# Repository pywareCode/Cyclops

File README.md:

ANDY
=======

Meet Andy, a multi-purpose humanoid robot built with a Raspberry Pi and a robosapien toy. Andy can walk, pick up and set down objects, take pictures, record video, and answer questions. Andy is voice controlled, so there is no need for a computer or smart phone to send him commands. Just say "Andy" wait for the beep, say your command, and Andy will do the rest.

Hardware
========

Andy is built out of inexpencive hardware, so no need for pocket loads of cash. A Robosapien is used for the body, making it easy to use and light in maintainance. A Raspberry Pi is the brain of Andy, making him a very intelligent machine. A cheap USB microphone is plugged into the Raspberry Pi's USB socket giving Andy ears. L298N and L293D motor drivers are used to control Andy's motors, and a MCP23017 chip is used to give the Raspberry Pi more General Purpose Input and Output ports (GPIO). Andy has vision with a Raspberry Pi CSI camera. With all of this powerful hardware, it makes a toy robot a very useful helper.

Software
========

Andy uses many different software packages to operate. Pocketsphinx is used for speech recognition, OpenCV is used for the vision, MySQL is used for Andy's database, and Python is used to combine everything together.

Learn More
==========

To learn more about the Andy Project and how you can make your own Andy, go to Andy's page on <a href="http://hackaday.io/project/1205">Hackaday.io</a>.
Also, check out <a href="http://youtu.be/Y5uNffNiwK4">a video</a> of Andy in action.

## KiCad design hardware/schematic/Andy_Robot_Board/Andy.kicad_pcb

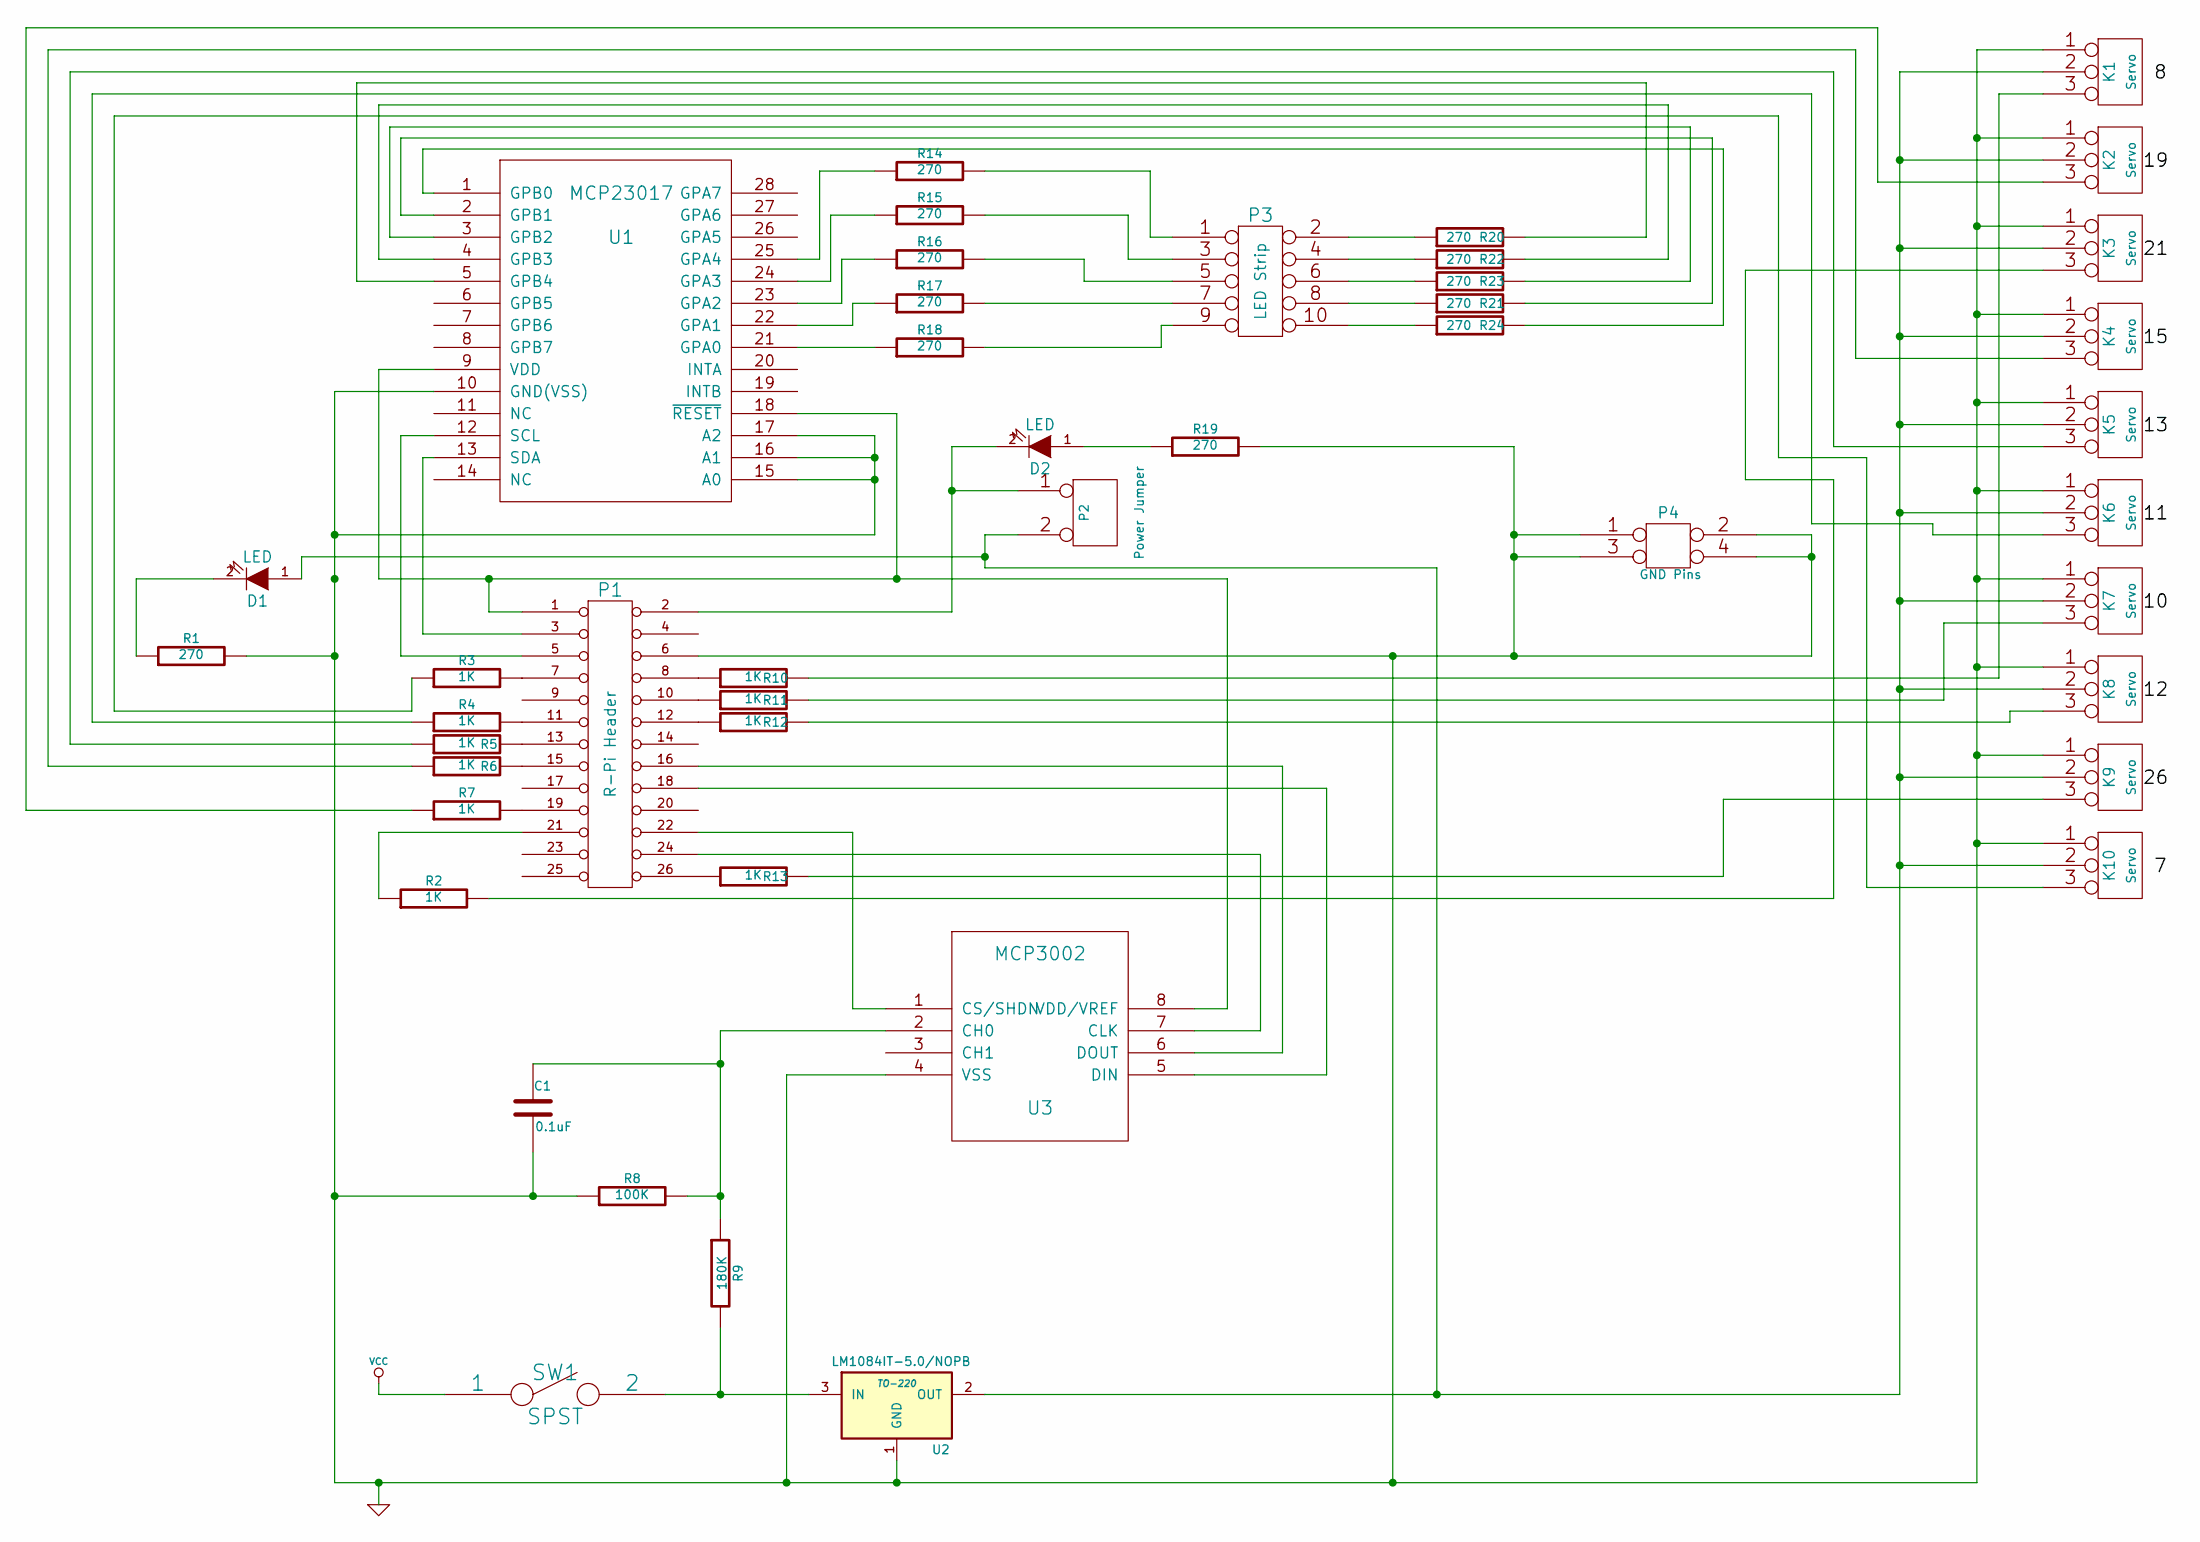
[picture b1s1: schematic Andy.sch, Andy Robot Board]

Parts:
C1: 0.1uF
D1, D2: LED
K1, K2, K3, K4, K5, K6, K7, K8, K9, K10: Servo
P1: R-Pi Header
P2: Power Jumper
P3: LED Strip
P4: GND Pins
R1, R14, R15, R16, R17, R18, R19, R20, R21, R22, R23, R24: 270
R2, R3, R4, R5, R6, R7, R10, R11, R12, R13: 1K
R8: 100K
R9: 180K
SW1: SPST
U1: MCP23017
U2: LM1084IT-5.0/NOPB; TO-220
U3: MCP3002

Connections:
GND: C1.2, K1.1, K2.1, K3.1, K4.1, K5.1, K6.1, K7.1, K8.1, K9.1, K10.1, P1.6, P4.1, P4.2, P4.3, P4.4, R1.2, R8.1, R19.2, U1.10 (GND(VSS)), U1.15 (A0), U1.16 (A1), U1.17 (A2), U2.1 (GND), U3.4 (VSS)
unnamed: R22.2, U1.3 (GPB2)
unnamed: R24.2, U1.1 (GPB0)
unnamed: P3.10, R24.1
unnamed: P3.8, R23.1
unnamed: P3.6, R22.1
unnamed: P3.4, R21.1
unnamed: P3.2, R20.1
unnamed: R20.2, U1.5 (GPB4)
unnamed: R21.2, U1.4 (GPB3)
unnamed: R23.2, U1.2 (GPB1)
unnamed: K10.3, R3.1
unnamed: K5.3, R5.1
unnamed: D2.1 (A), R19.1
unnamed: K4.3, R6.1
unnamed: P3.1, R14.2
unnamed: R14.1, U1.25 (GPA4)
unnamed: R15.1, U1.24 (GPA3)
unnamed: R16.1, U1.23 (GPA2)
unnamed: R17.1, U1.22 (GPA1)
unnamed: P3.3, R15.2
unnamed: P3.5, R16.2
unnamed: P3.7, R17.2
unnamed: P3.9, R18.2
unnamed: K2.3, R7.1
unnamed: D2.2 (K), P1.2, P2.1
unnamed: P1.7, R3.2
unnamed: P1.19, R7.2
unnamed: P1.15, R6.2
unnamed: P1.13, R5.2
unnamed: P1.11, R4.2
unnamed: D1.2 (K), R1.1
unnamed: K6.3, R4.1
unnamed: P1.26 (P22), R13.1
unnamed: K9.3, R13.2
unnamed: P1.12, R12.1
unnamed: P1.10, R11.1
unnamed: K1.3, R10.2
unnamed: P1.8, R10.1
unnamed: P1.21, R2.1
unnamed: K3.3, R2.2
unnamed: R18.1, U1.21 (GPA0)
unnamed: K7.3, R11.2
unnamed: K8.3, R12.2
unnamed: P1.24 (P20), U3.7 (CLK)
unnamed: C1.1, R8.2, R9.1, U3.2 (CH0)
unnamed: P1.22, U3.1 (CS/SHDN)
unnamed: P1.18, U3.5 (DIN)
unnamed: P1.16, U3.6 (DOUT)
unnamed: P1.3, U1.13 (SDA)
unnamed: P1.5, U1.12 (SCL)
unnamed: D1.1 (A), K1.2 (PM), K2.2 (PM), K3.2 (PM), K4.2 (PM), K5.2 (PM), K6.2 (PM), K7.2 (PM), K8.2 (PM), K9.2 (PM), K10.2 (PM), P2.2 (PM), U2.2 (OUT)
unnamed: P1.1, U1.9 (VDD), U1.18 (~RESET), U3.8 (VDD/VREF)
unnamed: R9.2, SW1.2, U2.3 (IN)

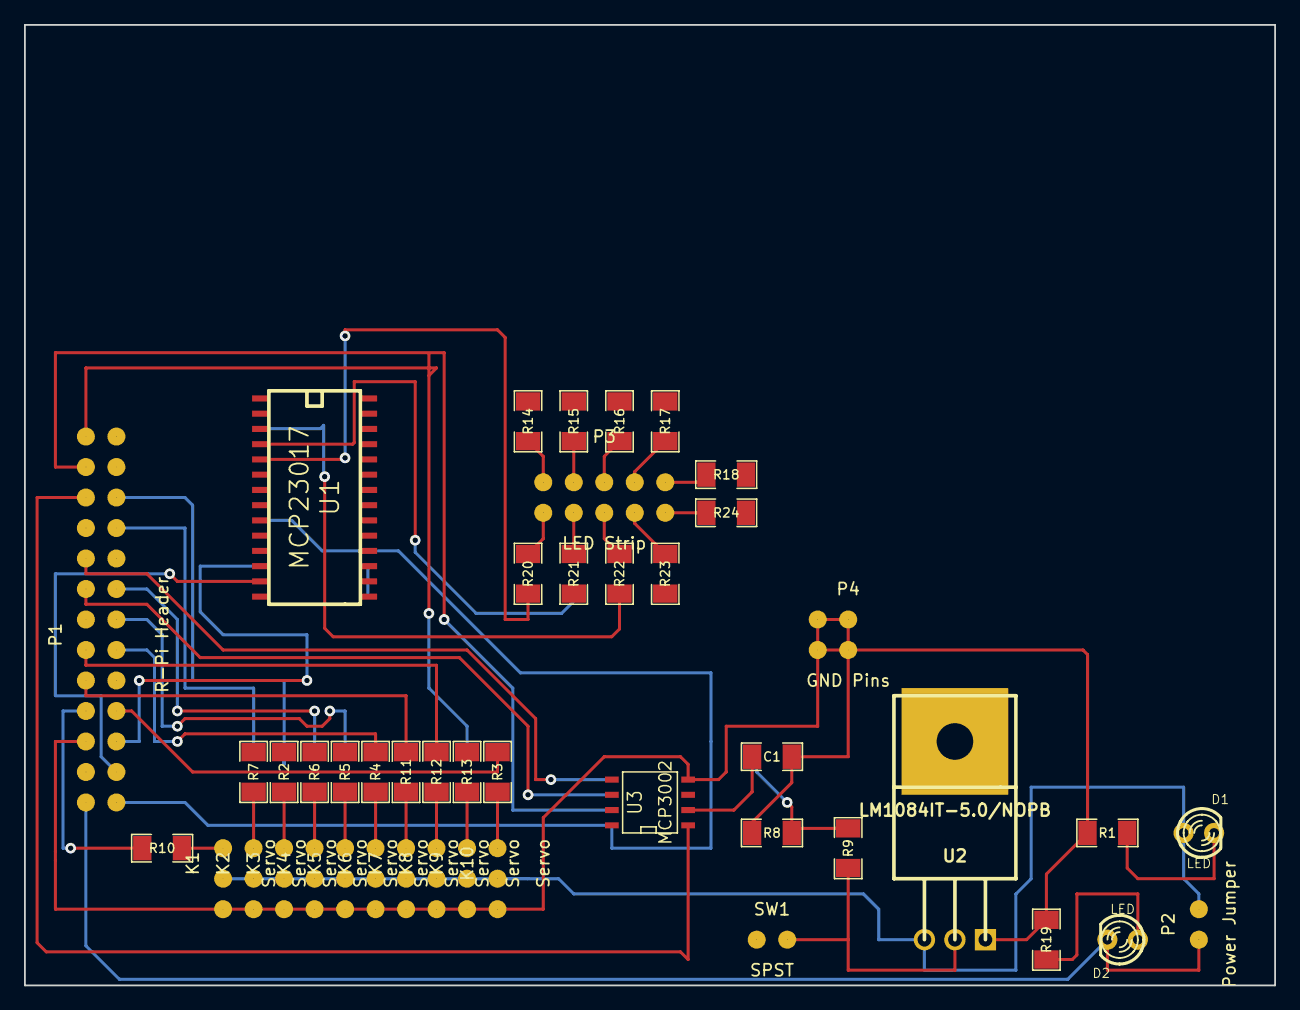
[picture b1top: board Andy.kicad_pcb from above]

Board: 2 copper layers, 104.1 x 80.0 mm, 45 parts (0 on the bottom side), 54 nets.

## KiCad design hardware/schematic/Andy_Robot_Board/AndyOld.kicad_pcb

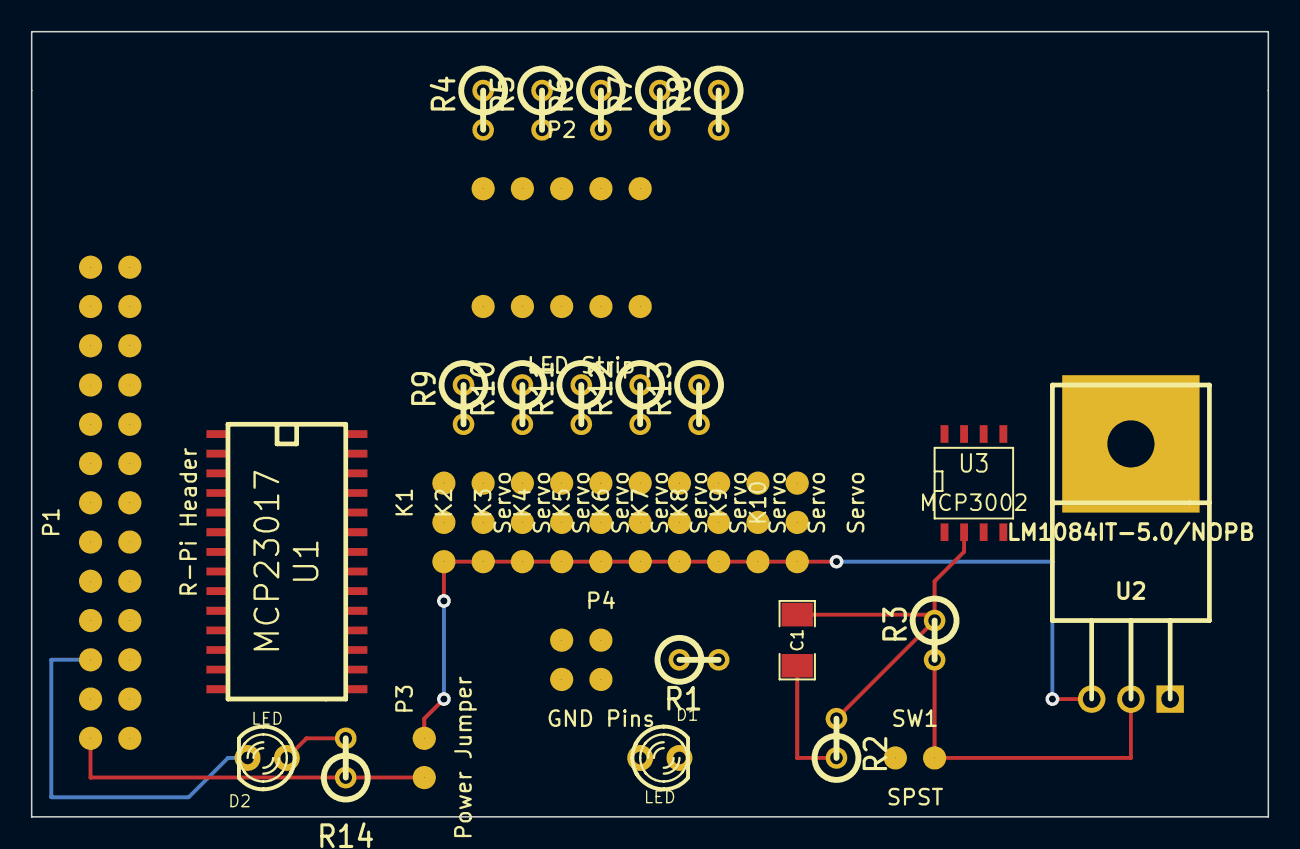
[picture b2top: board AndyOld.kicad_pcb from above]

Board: 2 copper layers, 80.0 x 50.8 mm, 35 parts (0 on the bottom side), 44 nets.

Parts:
C1: 0.1uF; SM1206
D1, D2: LED; LED-3MM
K1, K2, K3, K4, K5, K6, K7, K8, K9, K10: Servo; ServoHeader
P1: R-Pi Header; RaspberryPiHeader
P2: LED Strip; LED-Bar-Graph
P3: Power Jumper; jumper
P4: GND Pins; GNDheader
R1, R4, R5, R6, R7, R8, R9, R10, R11, R12, R13, R14: R; R1
R2: 100K; R1
R3: 180K; R1
SW1: SPST; jumper
U1: MCP23017; SO28
U2: LM1084IT-5.0/NOPB; TO220
U3: MCP3002; SO8N

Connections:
GND: C1.2, D1.2, D2.2, K6.3, K7.3, K8.3, K9.3, K10.3, P1.6, P4.1, P4.2, P4.3, P4.4, R2.1, U1.10, U1.15, U1.16, U1.17, U2.1, U3.4
unnamed: K9.2, P1.26
unnamed: K8.2, P1.12
unnamed: K7.2, P1.10
unnamed: K1.2, P1.21
unnamed: R4.1, U1.25
unnamed: R5.1, U1.24
unnamed: K1.3, K2.3, K3.3, K4.3, K5.3, K6.2, P1.8
unnamed: K10.2, P1.7
unnamed: K3.2, P1.15
unnamed: K4.2, P1.13
unnamed: K5.2, P1.11
unnamed: R6.1, U1.23
unnamed: R7.1, U1.22
unnamed: P2.1, R4.2
unnamed: P2.3, R5.2
unnamed: P2.5, R6.2
unnamed: P2.7, R7.2
unnamed: P2.9, R8.2
unnamed: R8.1, U1.21
unnamed: R11.2, U1.3
unnamed: R12.2, U1.2
unnamed: R13.2, U1.1
unnamed: P2.10, R13.1
unnamed: P2.8, R12.1
unnamed: P2.6, R11.1
unnamed: P2.4, R10.1
unnamed: P2.2, R9.1
unnamed: R9.2, U1.5
unnamed: R10.2, U1.4
unnamed: D2.1, R14.2
unnamed: P1.2, P3.1, R14.1
unnamed: D1.1, R1.1
unnamed: K2.2, P1.19
unnamed: R3.2, SW1.2, U2.3
unnamed: P1.18, U3.5
unnamed: P1.16, U3.6
unnamed: P1.3, U1.13
unnamed: P1.5, U1.12
unnamed: P1.1, U1.9, U1.18, U3.8
unnamed: P1.22, U3.1
unnamed: K1.1, K2.1, K3.1, K4.1, K5.1, K6.1, K7.1, K8.1, K9.1, K10.1, P3.2, R1.2, U2.2
unnamed: P1.24, U3.7
unnamed: C1.1, R2.2, R3.1, U3.2

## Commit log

2014-02-22 Added Google Speech-To-Text
2014-02-24 Added main.py and created functions
2014-02-24 added more cmds
2014-02-25 Added math
2014-02-26 Updated .gitgnore
2014-02-26 Deleted unwanted files
2014-03-01 Changed some files
2014-03-01 Added time knowledge
2014-03-01 Added me() function
2014-03-02 Added Walk() class and functions
2014-03-11 Added Motor Schematic and Arm() class
2014-03-11 Added Where() class
2014-03-11 Added Take() class
2014-03-11 Added Tell() class
2014-03-18 Added GPIO pin test and MCP23017 tst.
2014-03-19 added .autosave
2014-03-21 Added text-to-speech
2014-03-28 Updated text to speech
2014-04-07 Added motor control using L298N driver board. Also added PWM support
2014-04-08 Added Client Program
2014-04-08 Added server
2014-04-08 Removed .flac from .gitgnore for test
2014-04-09 Working Windows Version
    This is a working version for Windows. Use if revert is needed.
2014-04-18 Working Raspberry Pi version. MCP23017 now working with L293D in MCP.py
2014-04-30 Updated Schematic to 1.4
    Fixed control line errors, motor driver errors, and enable error.
2014-05-08 Worked on motor driving.
2014-05-13 Edited motor.py
2014-05-13 Updated language model
2014-05-20 Rearranged file system
2014-05-20 Added database file
2014-05-21 Added people and object access to database
2014-05-21 Updated schematic and language model
2014-05-22 Added complete 'WHO' command
2014-05-22 Added 'shutdown' command.
2014-05-23 Modified permissions and added sleep command
2014-05-23 Added error log and boot on start
2014-05-23 Added meet command
2014-05-23 Added age language model
2014-05-23 Added get_age()
2014-05-27 Worked on CLI and better performance
2014-05-28 Changed Client program
2014-05-28 Fixed NoneType error and worked on CLI
2014-05-29 removed client
2014-05-29 Finished Server
2014-06-01 Added configuration files and program
2014-06-11 Finished take picture command
2014-06-12 Made 'meet' command take pictures and save image path
2014-06-23 Updated schematic
2014-06-23 Changed walk slogan
2014-06-23 Change schematic file system
2014-06-27 Created temp directory for some files
2014-06-27 New schematic pic
2014-06-27 fix link
2014-06-27 darn link
2014-07-28 Schematic and Hardware update, also comments added
2014-07-28 Fixed hanging errors
2014-08-04 Worked on meet command
2014-08-05 Finished take command
2014-08-07 Made microphone use faster
2014-08-12 Fixed take video command saves
2014-08-20 Worked on Schematic and PCB
2014-08-20 Revert "Worked on Schematic and PCB"
    This reverts commit 378b42b77afeca410ef2adb0d70cc51d45ce2de5.
2014-08-20 Removed files from hardware
    Deleted files from here and moved them to ANDY-hardware
2014-09-06 Added servo control
2014-09-06 removed file
2014-09-13 Added LEDS
2014-09-13 Worked more on biped
2014-09-18 Created new branch
2014-09-18 Missed some files
2014-09-18 Added missing files
2014-09-29 Added Dropbox
2014-11-25 Long needed update in README
